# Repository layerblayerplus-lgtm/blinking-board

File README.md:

# blinking-board
I wanted to build this as i have never designed a pcb before 
This is the first PCB I have designed It is a simple LED chaser board. with text saying MYFIRST PCB.
I Learned a lot in this tutorial as i have never used any thing like kicad to design a pcb. 
I learned:
how to design a schematic
how to route diffrent components together on a pcb 
how to generate drill files 
and how to render my pcb.

                                 schematic

                                     pcb

                               order info/image

|Amount|Part                       |Link                                                                                                                                                                                                                                                                                                                                        |
|------|---------------------------|--------------------------------------------------------------------------------------------------------------------------------------------------------------------------------------------------------------------------------------------------------------------------------------------------------------------------------------------|
|1x    |NE555P                     | https://www.digikey.ca/en/products/detail/texas-instruments/NE5534AP/378264?gclsrc=aw.ds&gad_source=4&gad_campaignid=17336435733&gbraid=0AAAAADrbLljDHfacCu98DnK46yYAiNN37&gclid=CjwKCAjw857RBhAgEiwAI-1yKCxYrpwuLAIqkdFffcmWrlOUvPUjZy6fNLhgflxf62_DjCdUeT-yBRoCY0oQAvD_BwE|
|1x    | CD4017                    | https://www.digikey.ca/en/products/detail/texas-instruments/CD4017BNSR/525881?gclsrc=aw.ds&gad_source=1&gad_campaignid=17336435733&gbraid=0AAAAADrbLli9eV0U9YydH_Gi2Pu6vT9lb&gclid=CjwKCAjw857RBhAgEiwAI-1yKEFHFKrDZmENSb6Irk_XqSna2J6SexJ6_dY74dbEH2ZHTAESL-auxhoCDvkQAvD_BwE|
|1x    | Conn_01x02_Socket         | https://www.digikey.ca/en/products/detail/harwin-inc/M50-3030242/7043990?gclsrc=aw.ds&gad_source=1&gad_campaignid=17336435733&gbraid=0AAAAADrbLli9eV0U9YydH_Gi2Pu6vT9lb&gclid=CjwKCAjw857RBhAgEiwAI-1yKOKAOM5ycakR_TIsvxZ-_LortzUTmvxOxrnKzlbsM__oUnLh41udrxoClSYQAvD_BwE|
|1x    | Conn_01x01_Socket         | https://www.digikey.ca/en/products/detail/3m/929870-01-01-RA/1239297?gclsrc=aw.ds&gad_source=1&gad_campaignid=20557660208&gbraid=0AAAAADrbLlghw5W8IU891OcnWO9k1tg4W&gclid=CjwKCAjw857RBhAgEiwAI-1yKGBakMZoKuv8ROv9sMHdHia73StzqqZ4MR1u3N-AI8TLJU2ulumzIxoC0OAQAvD_BwE|
|1x    | 1uF electrolytic capacitor| https://canada.newark.com/multicomp-pro/mcrh63v105m5x11/aluminum-electrolytic-capacitor/dp/70K9783?&CMP=KNC-GCA-PMAX-SHOPPING-ONBOARD-COMP-Passives-NEW&gad_source=4&gad_campaignid=23072788681&gbraid=0AAAAAD5U_g3dmjRABjlUmhYrklgSELEmQ&gclid=CjwKCAjw857RBhAgEiwAI-1yKDafVkSZ6bSH6IqRWV6y1I__VvVVlMmQyR6a29TBU7ZBOuOQsFD6LBoCPIoQAvD_BwE  |
|1x    | 0.01 uF capacitor         | https://canada.newark.com/multicomp/mc0805y103m101a2-54mm/ceramic-capacitor-0-01uf-100v/dp/46P6661?&CMP=KNC-GCA-GEN-SHOPPING-PMAX-CLM-NCA-WF4799466&gad_source=4&gad_campaignid=23881382570&gbraid=0AAAAAD8yeHn4gXpNvGW_9arXEgFB-f0bE&gclid=CjwKCAjw857RBhAgEiwAI-1yKGyOpQkHTAFZOnUlkoaVHCC1gItcL47PEgV--doMpDf5_KtqjoYiPRoCuTsQAvD_BwE  |
|1x    | 1k ohm resistor https     |://www.digikey.ca/en/products/detail/yageo/MFR-25FBF52-1K/13011|
|1x    | 470 ohm resistor https    |://www.digikey.ca/en/products/detail/stackpole-electronics-inc/CF14JT470R/1741440?gclsrc=aw.ds&gad_source=1&gad_campaignid=17336435733&gbraid=0AAAAADrbLli9eV0U9YydH_Gi2Pu6vT9lb&gclid=CjwKCAjw857RBhAgEiwAI-1yKGVDe_vsmDamDZs0RYLGy-P_LA1DTveZcQqoUFegQ9pAzUeBEfvqZRoCMYMQAvD_BwE|
|1x    | potentiometer             | https://www.digikey.ca/en/products/detail/bourns-inc/PDB181-K415K-503B/4699119?gclsrc=aw.ds&gad_source=1&gad_campaignid=20572521725&gbraid=0AAAAADrbLlgU80Fgg_ZZC3hnD8Q9Pdjic&gclid=CjwKCAjw857RBhAgEiwAI-1yKBkQoTf2LaBqW23FCYreyX4lMrzQ9FPcC1UHQ5OCIpLQ0JAP41y-YRoCH_cQAvD_BwE|
|10x   | LEDS                      | https://ca.robotshop.com/products/led-assortment-set-25pk?gad_source=1&gad_campaignid=20159687494&gbraid=0AAAAAD_f_xy1iMiiwn_VorgSJIpXvRzDT&gclid=CjwKCAjw857RBhAgEiwAI-1yKJndrNXQRV32CD8v7o-xFeJOGVIy5UZixvlGWDBzWm7VK62wCOhYBBoC3u4QAvD_BwE                                                                                              |

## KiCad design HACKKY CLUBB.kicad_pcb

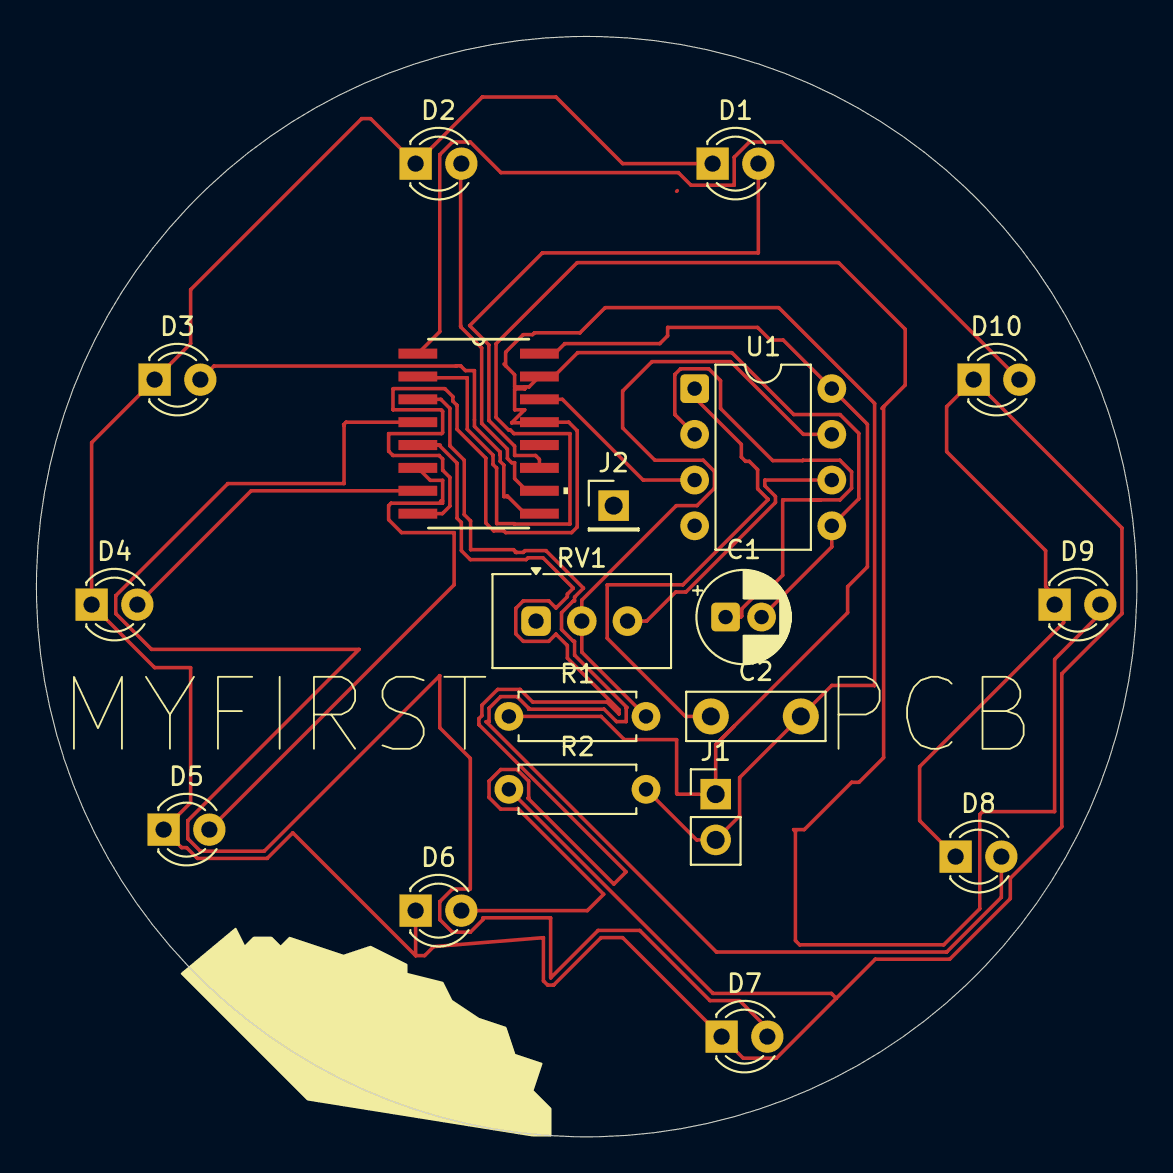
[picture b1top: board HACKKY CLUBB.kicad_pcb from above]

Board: 2 copper layers, 61.1 x 61.1 mm, 19 parts (0 on the bottom side), 18 nets.

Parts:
C1: C_Polarized; CP_Radial_D5.0mm_P2.00mm
C2: C_Small; C_Disc_D7.5mm_W2.5mm_P5.00mm
D1, D2, D3, D4, D5, D6, D7, D8, D9, D10: LED; LED_D3.0mm
J1: Conn_01x02_Socket; PinHeader_1x02_P2.54mm_Vertical
J2: Conn_01x01_Socket; PinHeader_1x01_P2.54mm_Vertical
R1: R; R_Axial_DIN0207_L6.3mm_D2.5mm_P7.62mm_Horizontal
R2: 470; R_Axial_DIN0207_L6.3mm_D2.5mm_P7.62mm_Horizontal
RV1: R_Potentiometer; Potentiometer_Vishay_T93YA_Vertical
U1: NE555P; DIP-8_W7.62mm
U2: CD4017BNSR; NS16

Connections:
+5V: J1.1, R1.1, U1.8 (VCC), U2.16 (VDD)
GND: C1.2, C2.2, J1.2, R2.2, U1.5 (CONT), U2.8 (VSS), U2.13 (CLOCKINHIBIT), U2.15 (RESET)
unnamed: D1.2 (A), U2.11 (9)
unnamed: D1.1 (K), D2.1 (K), D3.1 (K), D4.1 (K), D5.1 (K), D6.1 (K), D7.1 (K), D8.1 (K), D9.1 (K), D10.1 (K), R2.1
unnamed: D2.2 (A), U2.10 (4)
unnamed: D3.2 (A), U2.9 (8)
unnamed: D4.2 (A), U2.7 (3)
unnamed: D5.2 (A), U2.6 (7)
unnamed: D6.2 (A), U2.5 (6)
unnamed: D7.2 (A), U2.4 (2)
unnamed: D8.2 (A), U2.3 (0)
unnamed: D9.2 (A), U2.2 (1)
unnamed: D10.2 (A), U2.1 (5)
unnamed: J2.1 (Pin_1_1), U1.3 (OUT), U2.14 (CLOCK)
unnamed: R1.2, RV1.1, RV1.2, U1.7 (DISCH)
unnamed: C2.1, U1.1 (GND)
unnamed: RV1.3, U1.6 (THRES)
unnamed: C1.1, U1.2 (TRIG)

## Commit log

2026-06-04 Rename hackky clubb.kicad_pcb to BLINKING BOARD.kicad_pcb
2026-06-04 Rename hackky clubb.kicad_sch to BLINKING BOARD.kicad_sch
2026-06-04 Rename iLoveZIP_Create.zip to read GERBER.zip
2026-06-04 Rename image.png to READimage.png
2026-06-04 Rename HACKKY CLUBB.kicad_sch to READBLINKING BOARD.kicad_sch
2026-06-04 Rename BLINKING BOARD.kicad_pcb to READBLINKING BOARD.kicad_pcb
2026-06-05 Create PCB
2026-06-05 Rename PCB to PCB./temp
2026-06-05 Rename READBLINKING BOARD.kicad_pcb to PCB./READBLINKING BOARD.kicad_pcb
2026-06-05 Rename READBLINKING BOARD.kicad_sch to PCB./BLINKING BOARD.kicad_sch
2026-06-05 Rename READBLINKING BOARD.kicad_pcb to BLINKING BOARD.kicad_pcb
2026-06-05 Rename read GERBER.zip to PCB./ GERBER.zip
2026-06-05 Create temp
2026-06-05 Rename READimage.png to ASSETS/image.png
2026-06-10 Rename BOM.md to BOM.csv
